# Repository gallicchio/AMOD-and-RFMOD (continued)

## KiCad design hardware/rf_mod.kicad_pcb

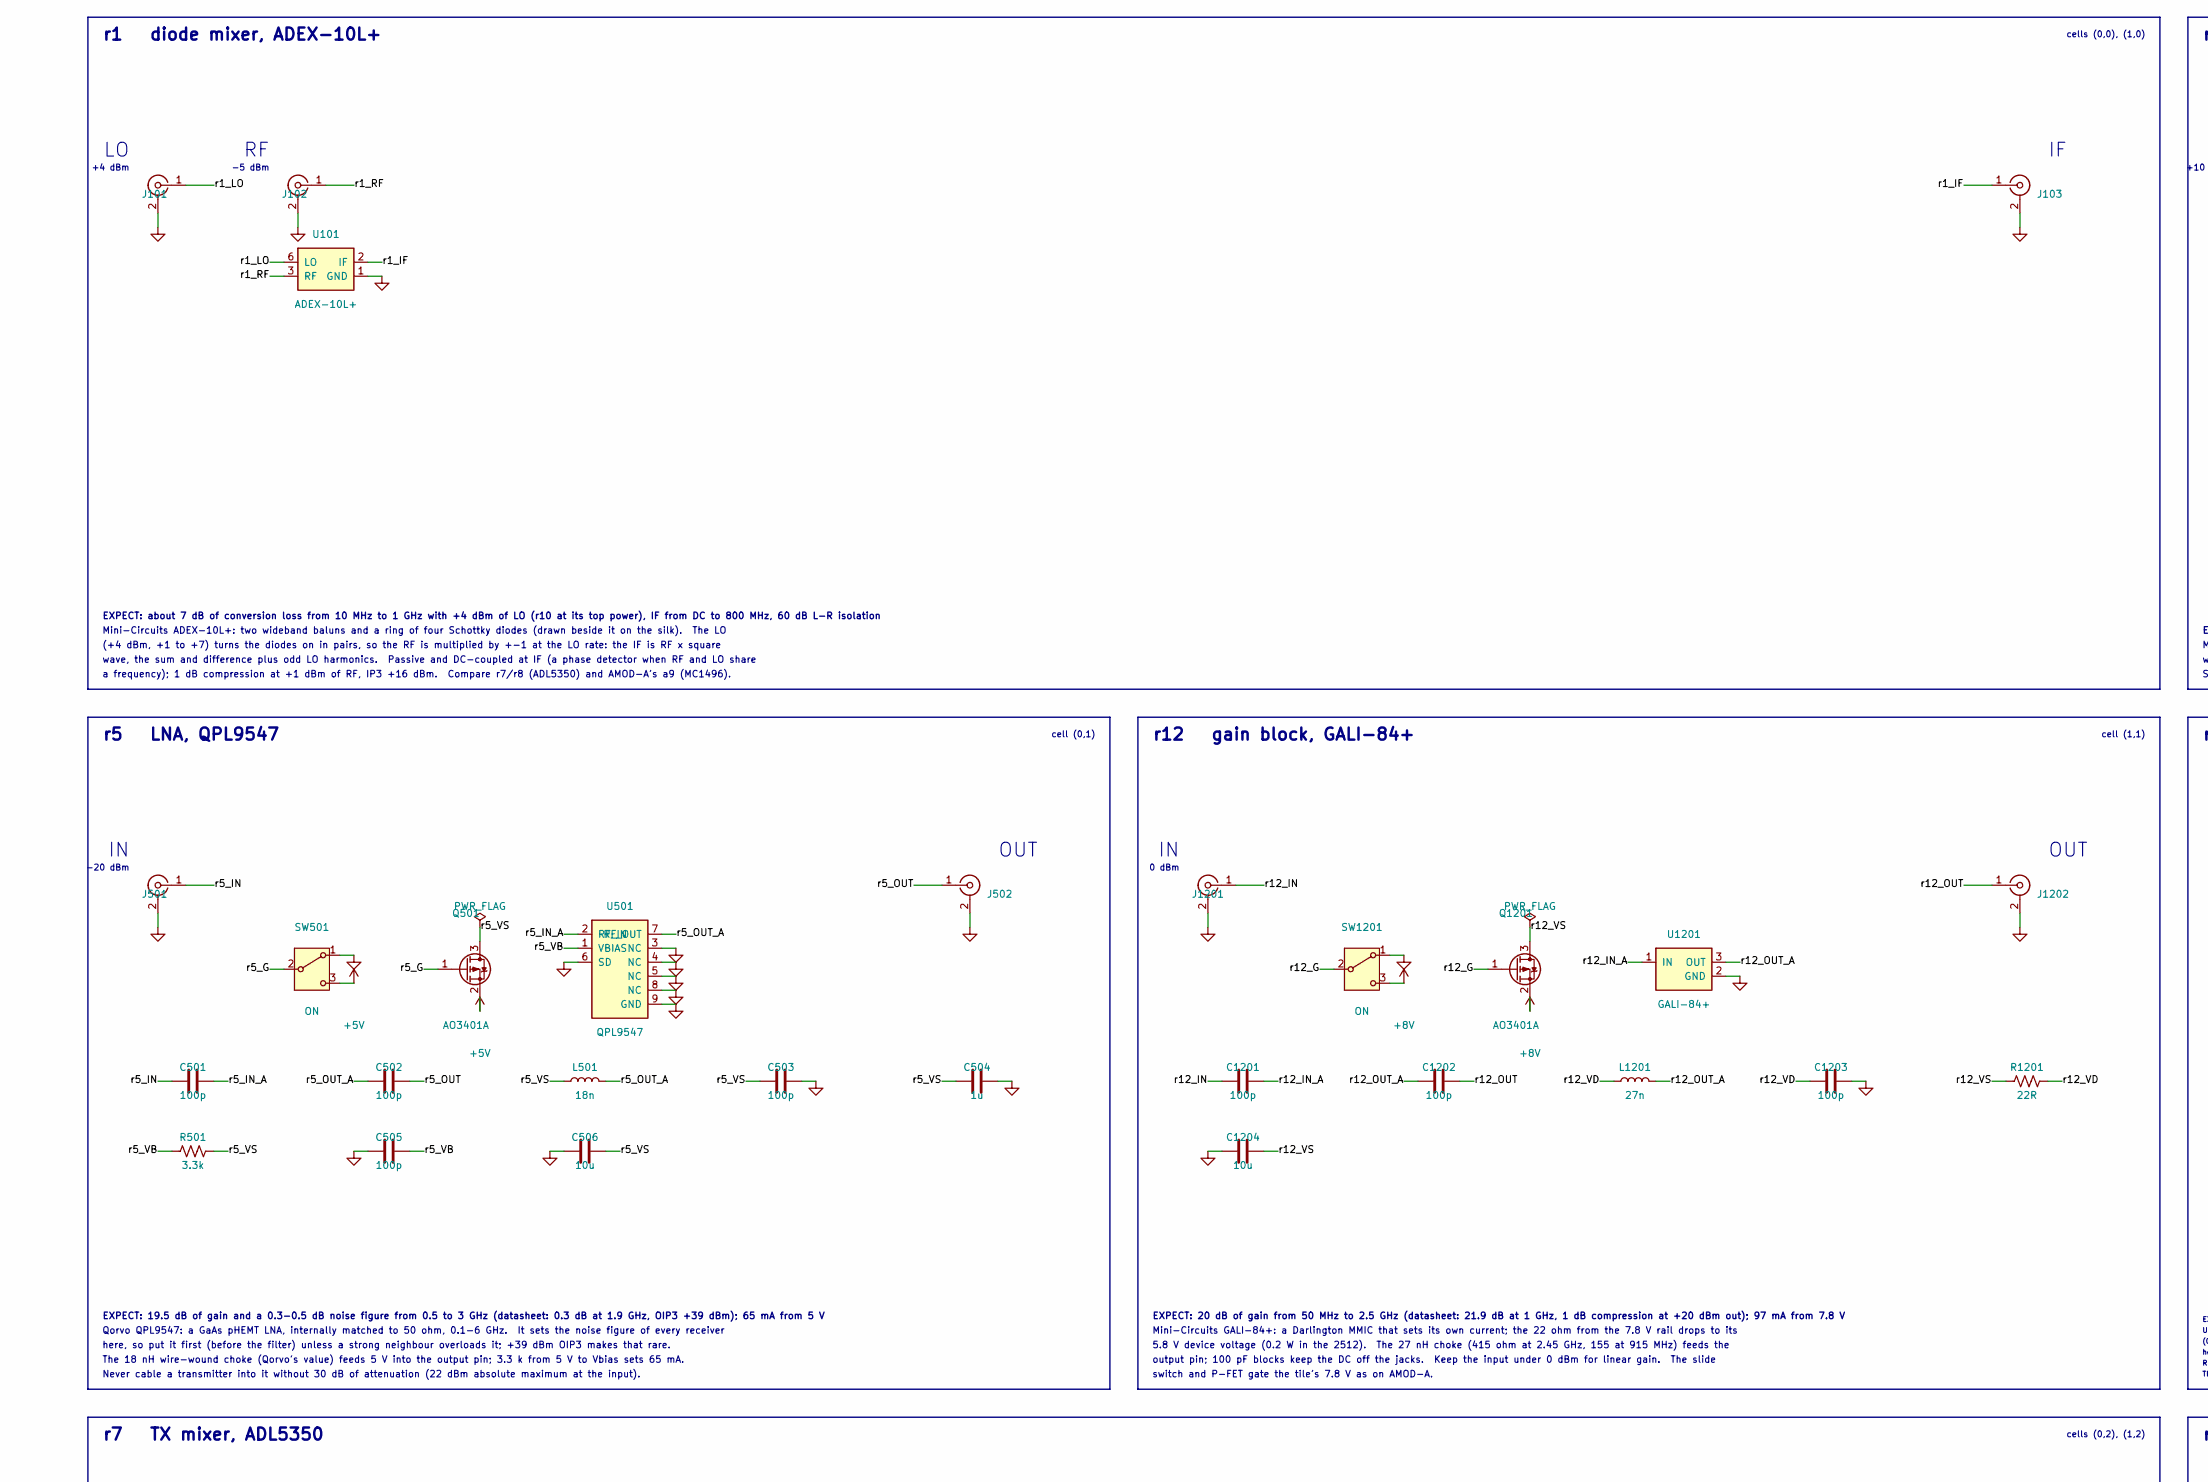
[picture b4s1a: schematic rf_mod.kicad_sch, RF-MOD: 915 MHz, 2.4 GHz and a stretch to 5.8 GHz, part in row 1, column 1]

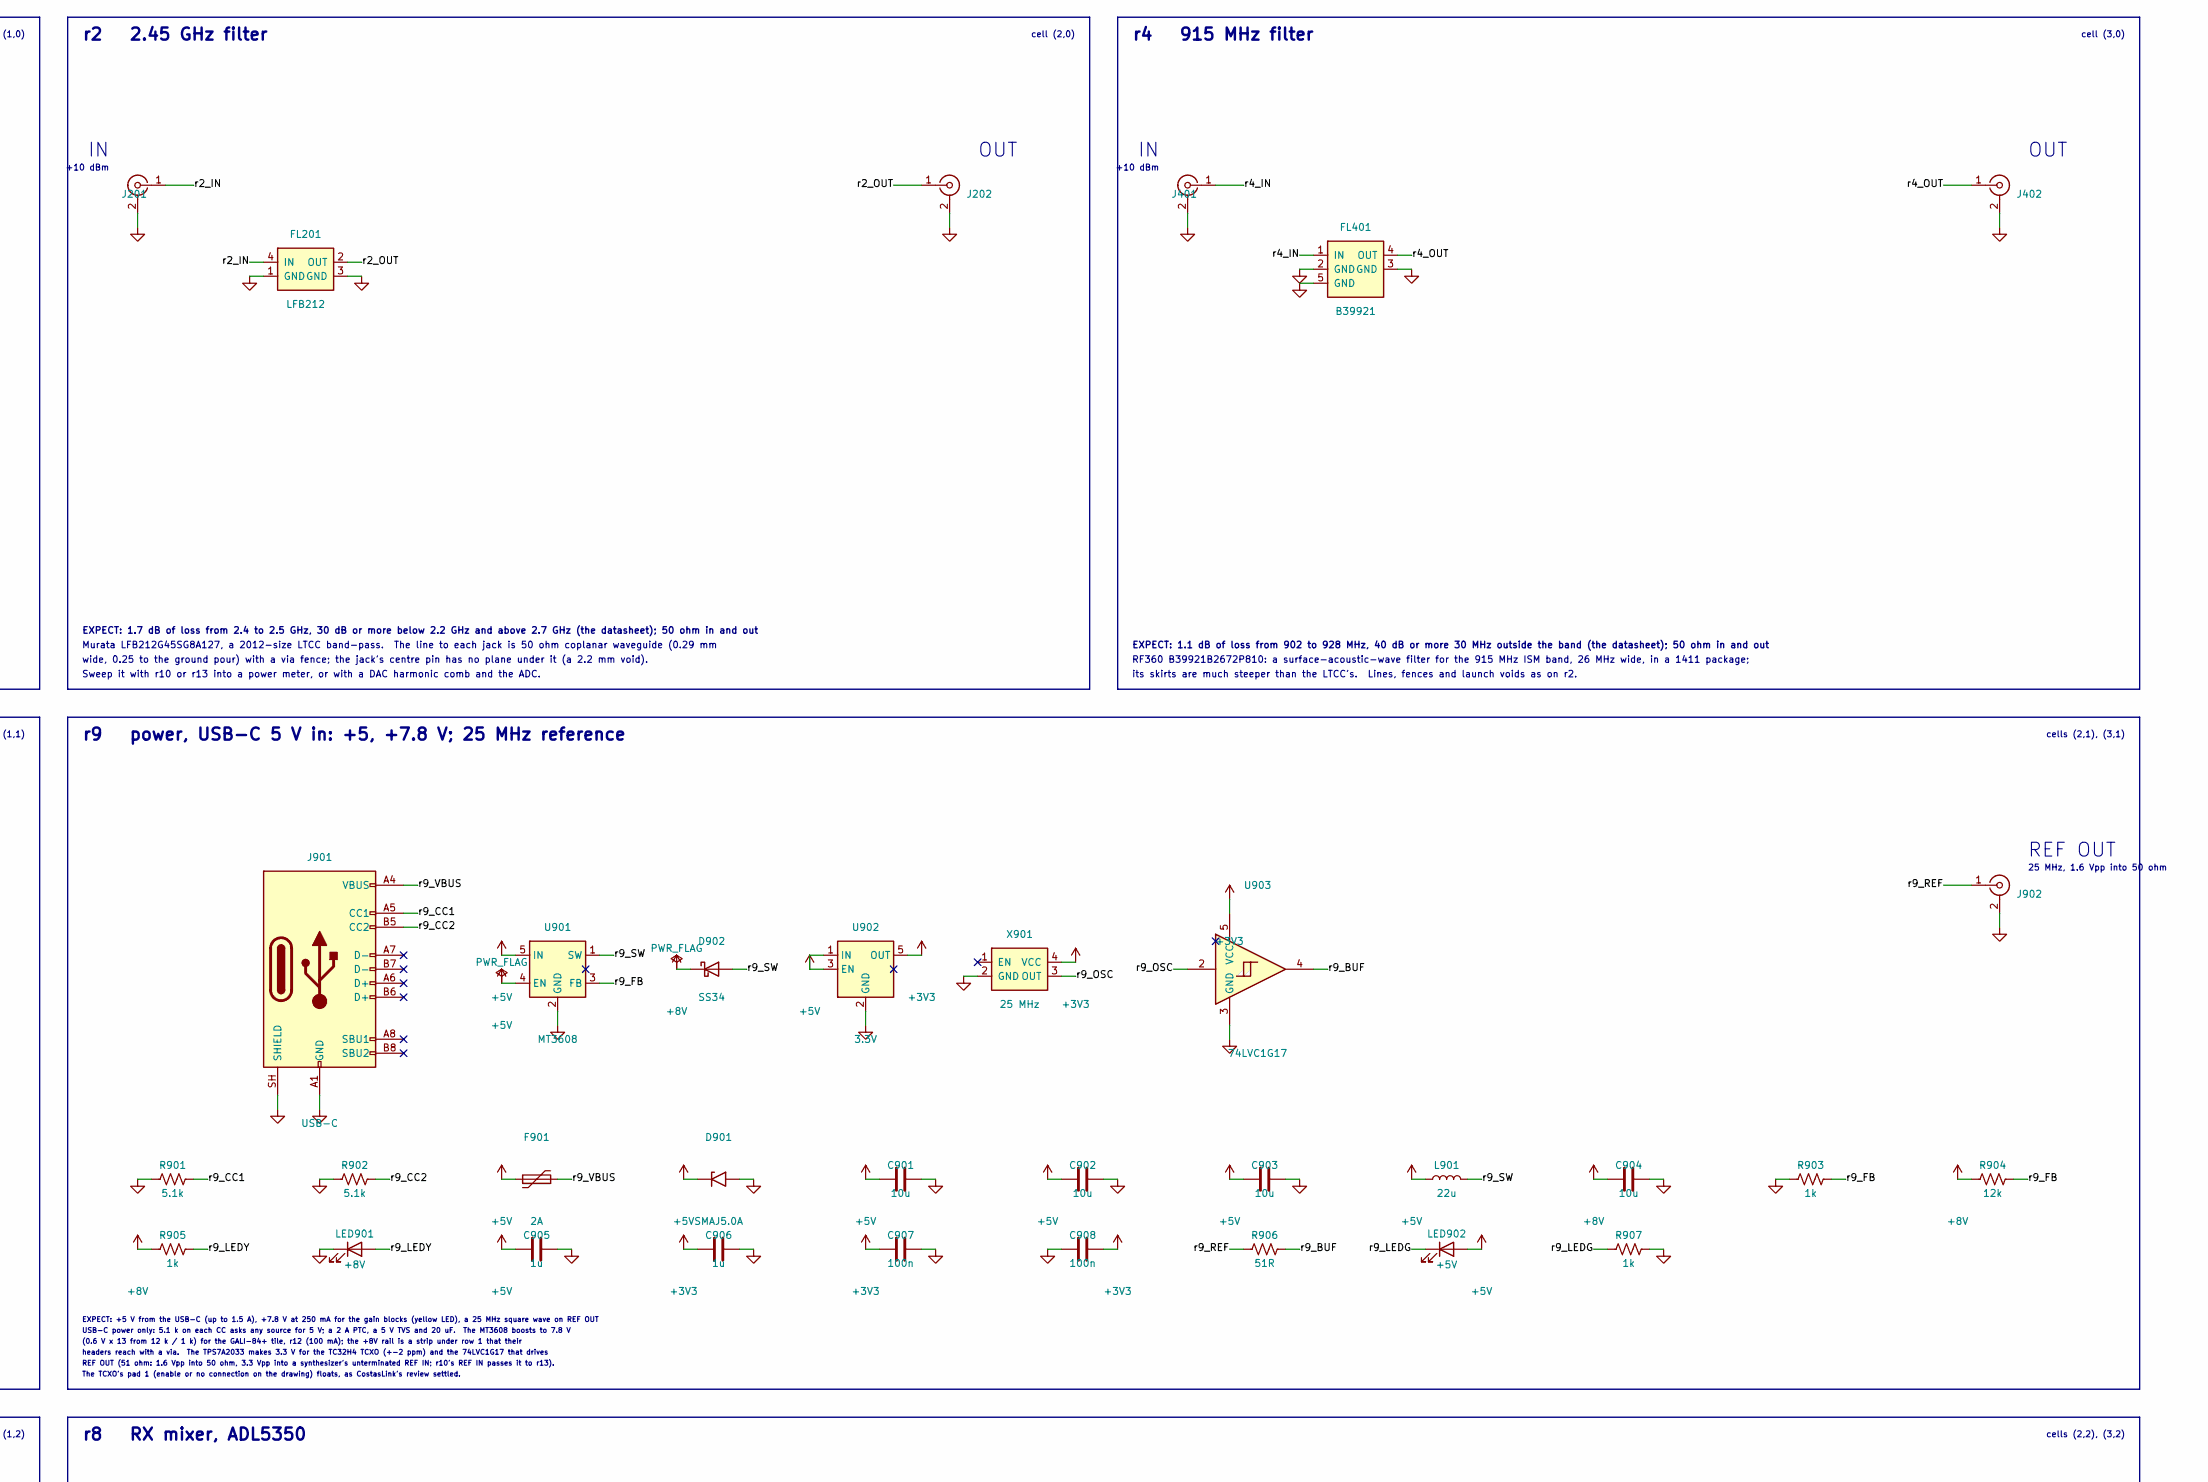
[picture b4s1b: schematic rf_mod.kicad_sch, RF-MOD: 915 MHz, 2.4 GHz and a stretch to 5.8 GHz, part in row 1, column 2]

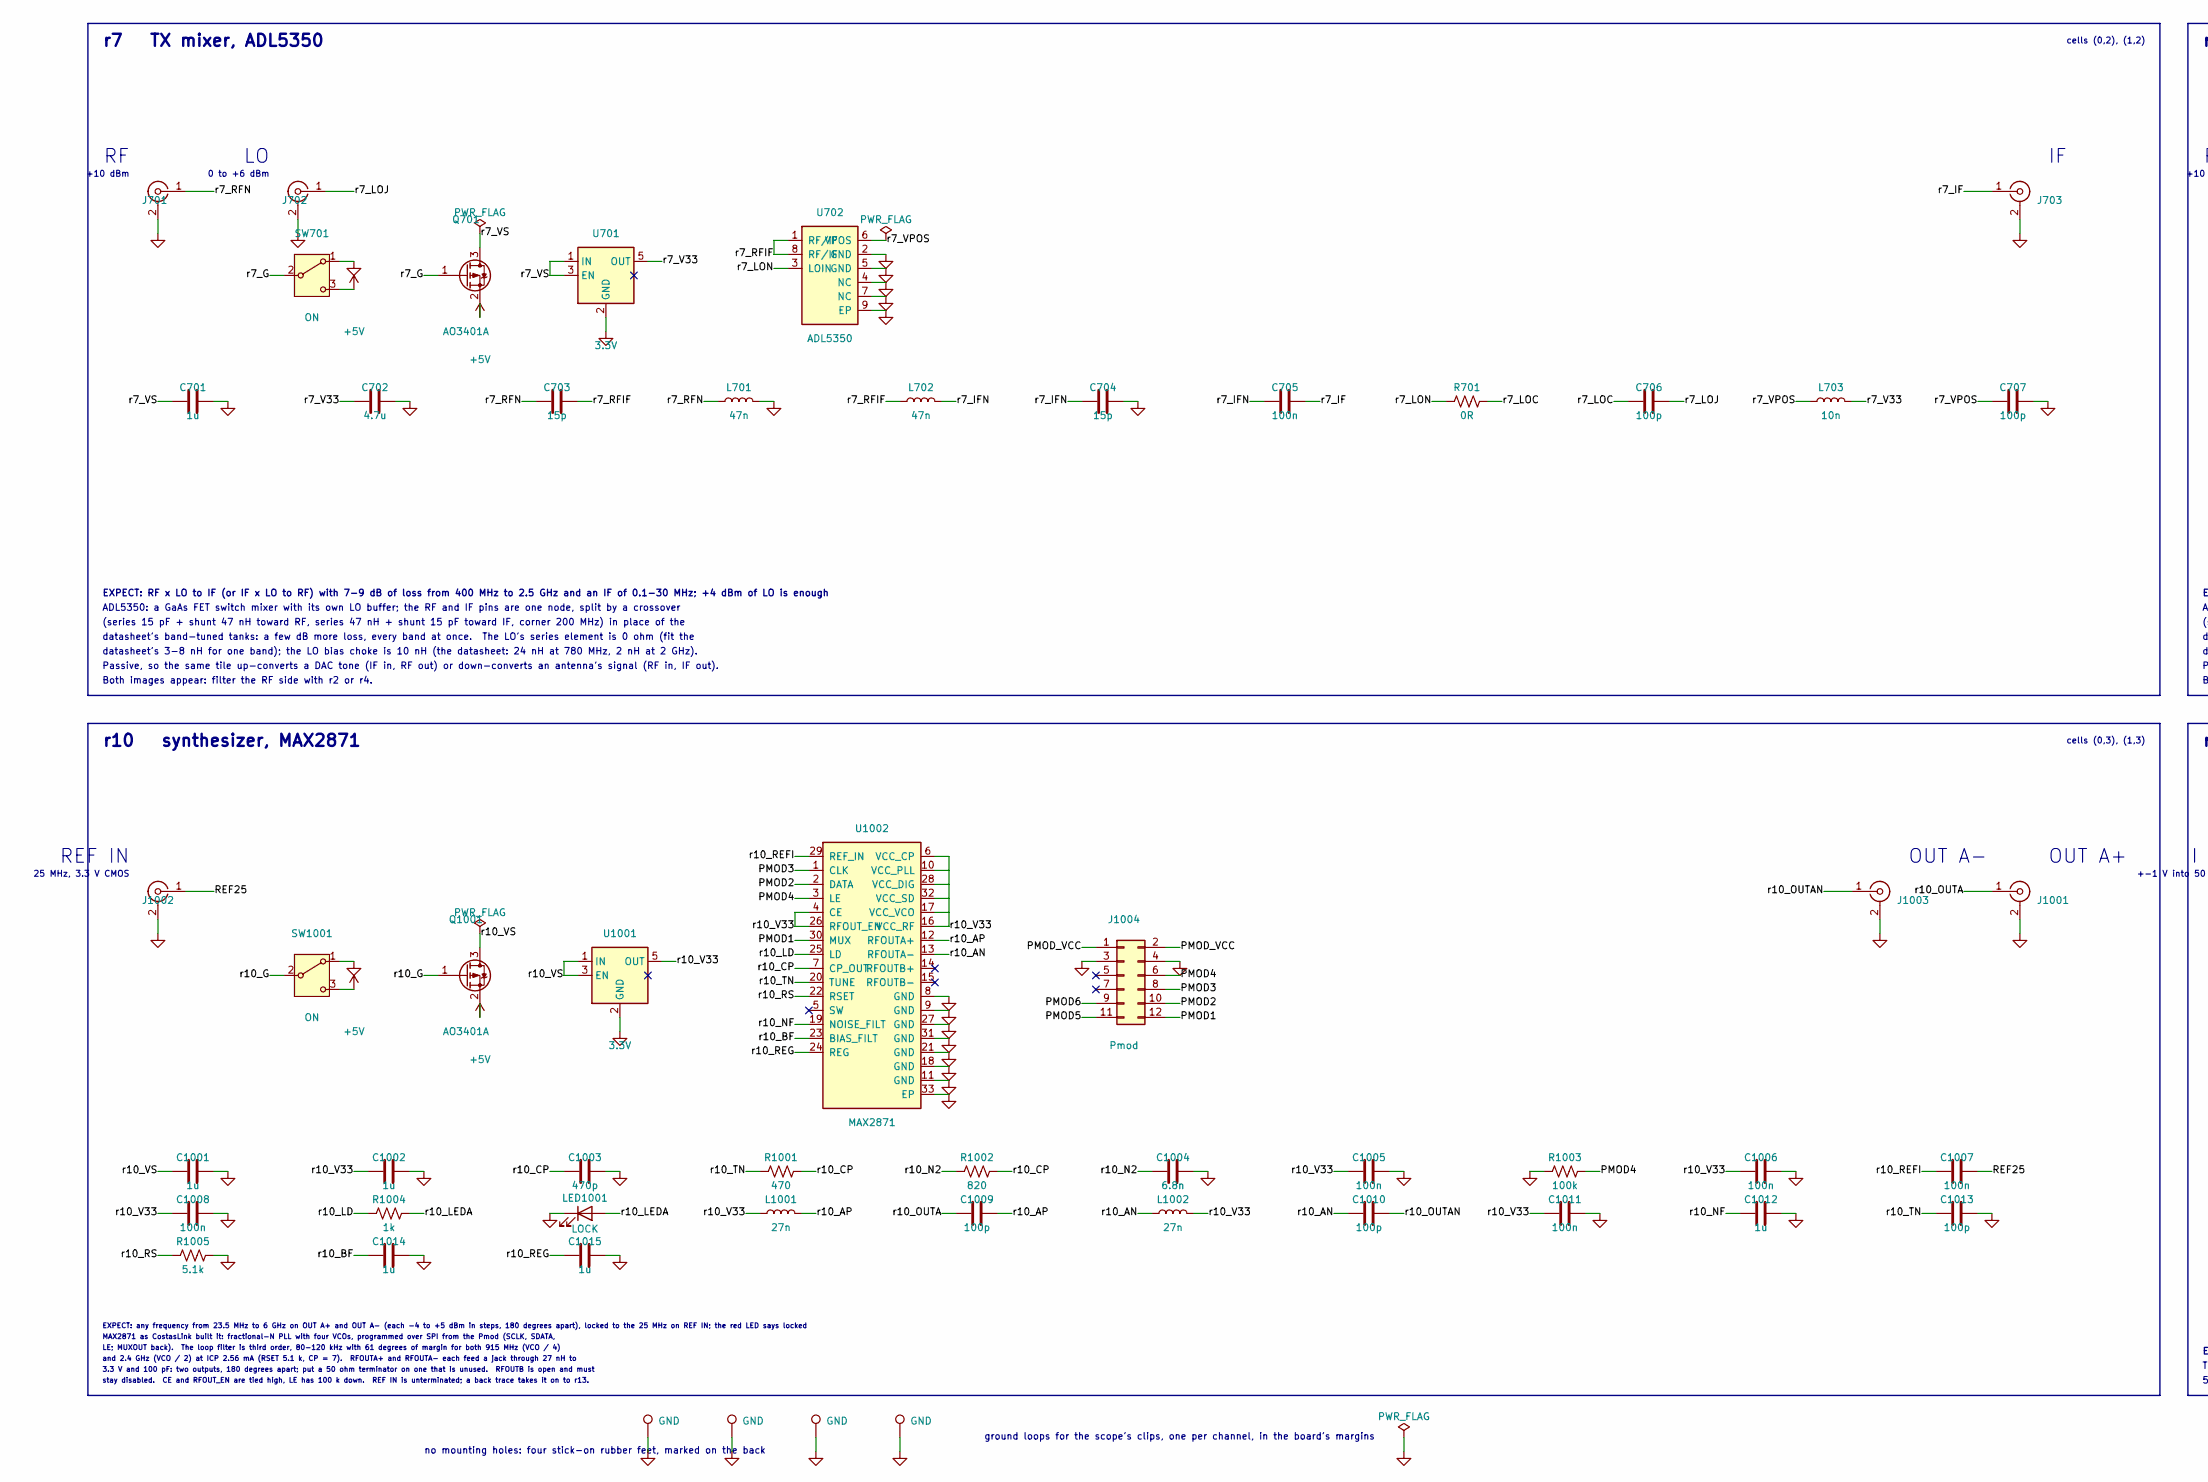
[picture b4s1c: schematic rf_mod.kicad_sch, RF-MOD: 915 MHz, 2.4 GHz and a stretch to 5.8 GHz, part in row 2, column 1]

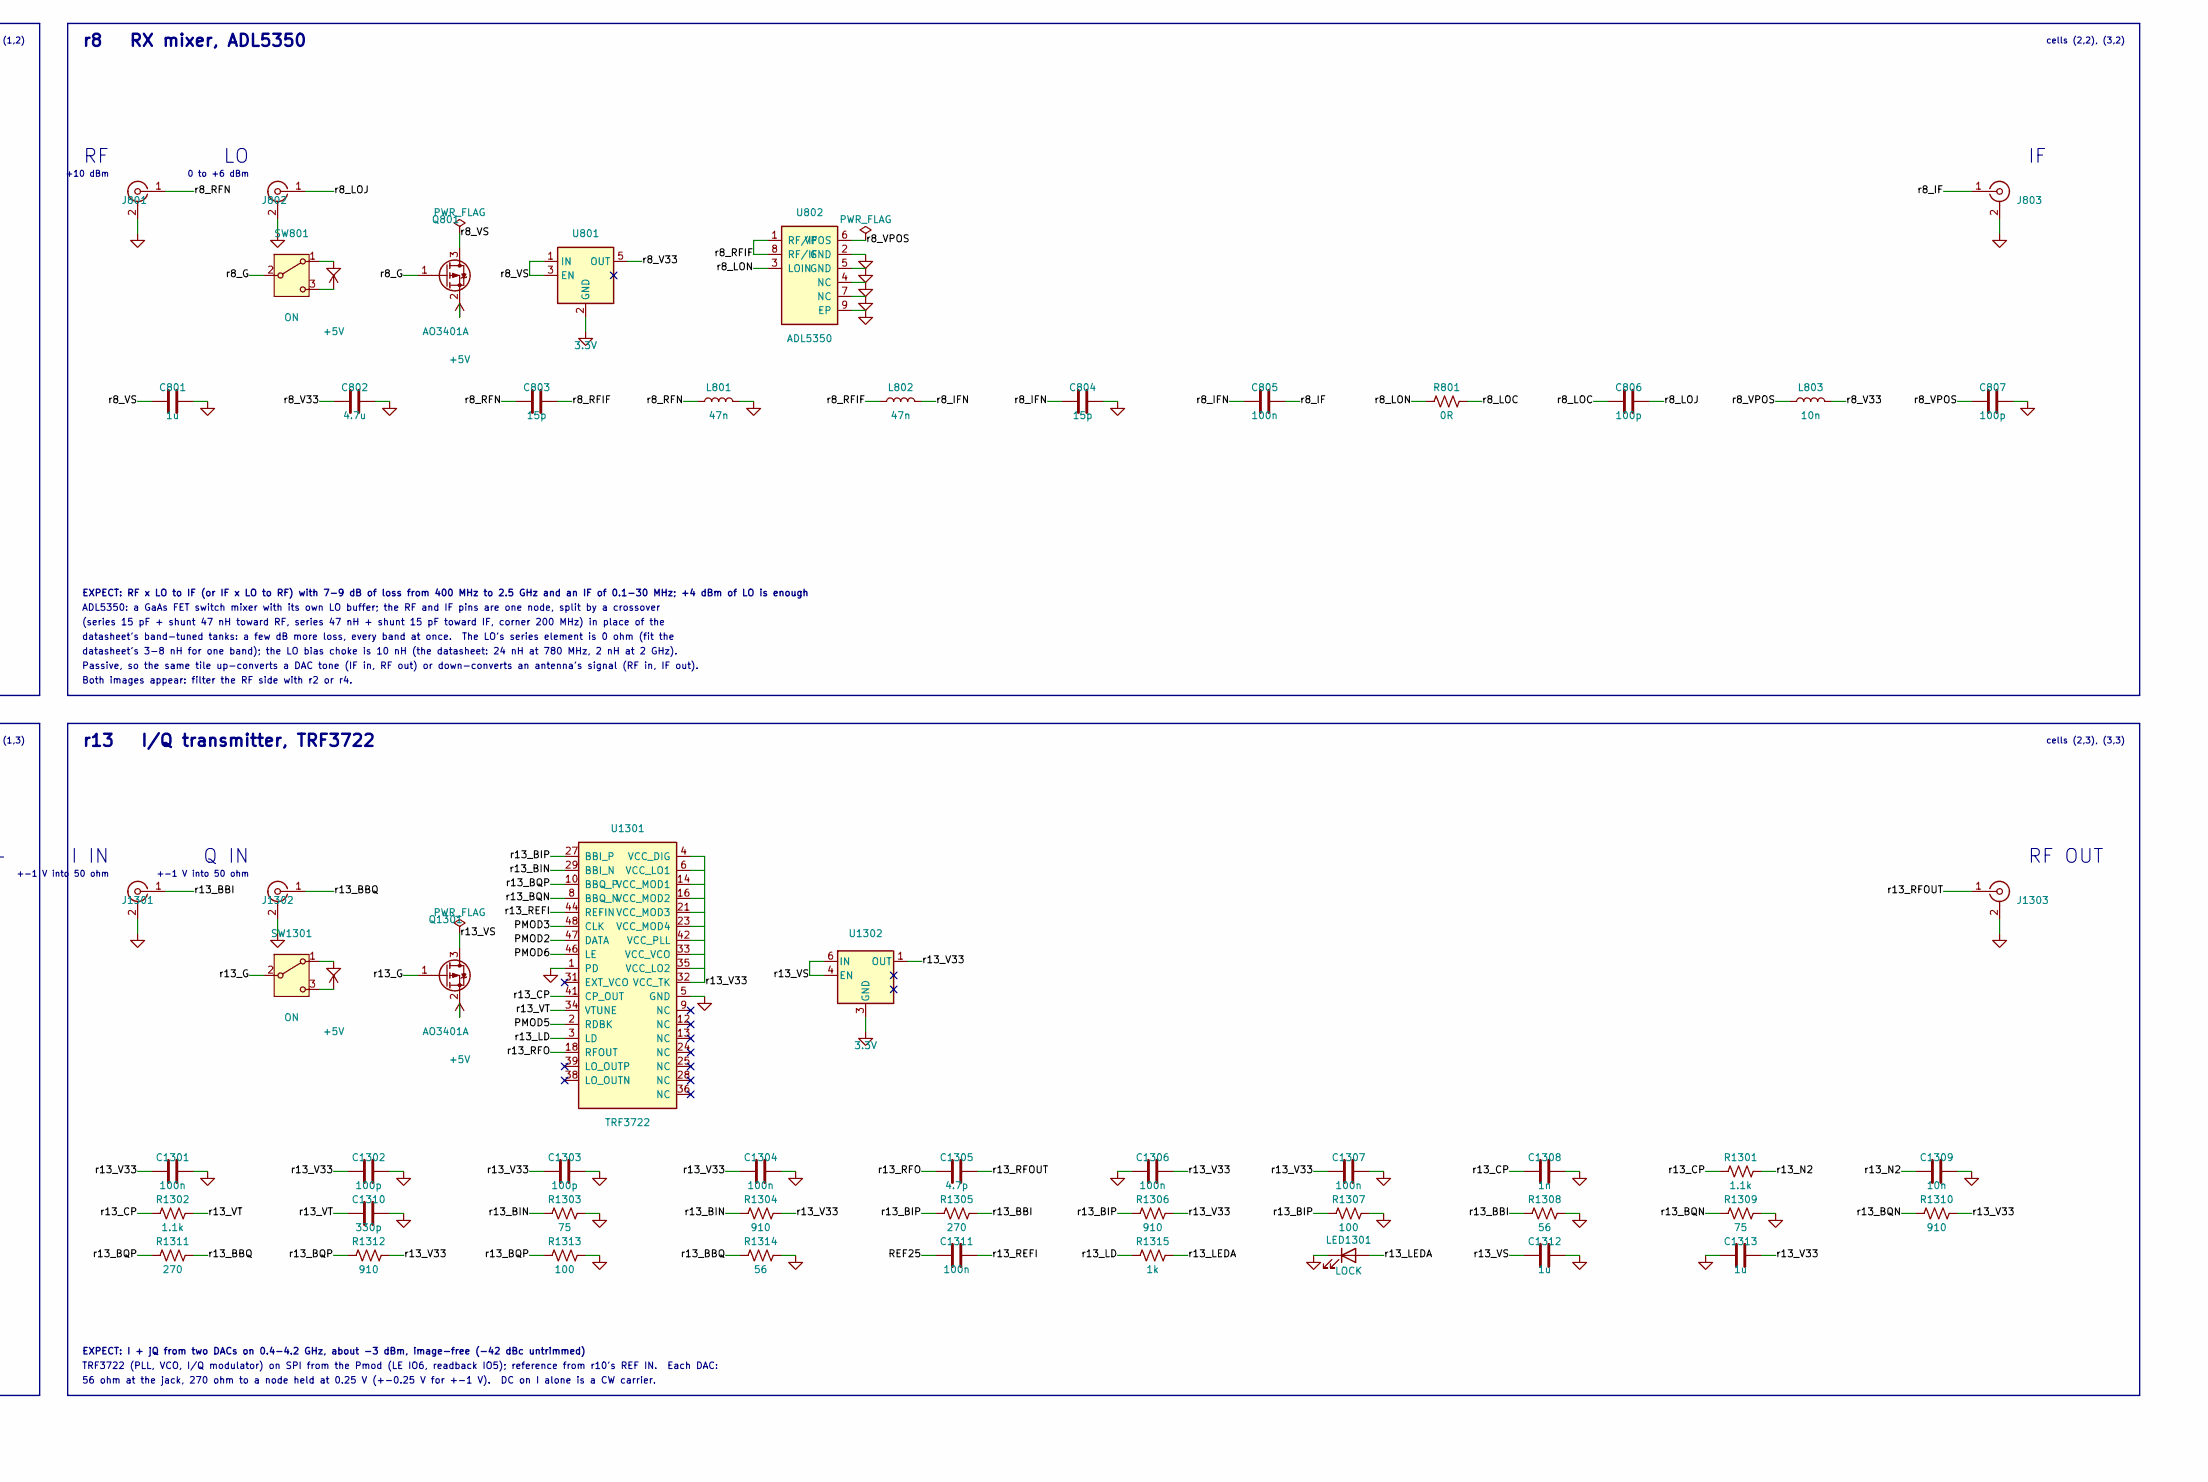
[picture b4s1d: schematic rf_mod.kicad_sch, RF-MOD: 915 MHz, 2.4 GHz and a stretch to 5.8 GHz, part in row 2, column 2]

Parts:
C501, C502, C503, C505, C706, C707, C806, C807, C1009, C1010, C1201, C1202, C1203, C1302, C1303: 100p; C_0402_1005Metric; MPN 0402CG101J500NT; LCSC C1546
C504, C1012, C1014, C1015: 1u; C_0402_1005Metric; MPN CL05A105KP5NNNC; LCSC C14445
C506, C901, C902, C903, C904, C1204: 10u; C_0805_2012Metric; MPN CL21A106KAYNNNE; LCSC C15850
C701, C801, C905, C906, C1001, C1002: 1u; C_0805_2012Metric; MPN CL21B105KBFNNNE; LCSC C28323
C702, C802: 4.7u; C_0805_2012Metric; MPN CL21A475KAQNNNE; LCSC C1779
C703, C704, C803, C804: 15p; C_0402_1005Metric; MPN 0402CG150J500NT; LCSC C1548
C705, C805, C1005, C1006, C1007, C1008, C1011, C1301, C1304, C1306, C1307, C1311: 100n; C_0402_1005Metric; MPN CL05B104KO5NNNC; LCSC C1525
C907, C908: 100n; C_0603_1608Metric; MPN CC0603KRX7R9BB104; LCSC C14663
C1003: 470p; C_0603_1608Metric; MPN 0603CG471J500NT; LCSC C36252
C1004: 6.8n; C_0603_1608Metric; MPN GRM1885C1H682JA01D; LCSC C162241
C1013: 100p; C_0603_1608Metric; MPN CL10C101JB8NNNC; LCSC C14858
C1305: 4.7p; C_0402_1005Metric; MPN 0402CG4R7C500NT; LCSC C1569
C1308: 1n; C_0402_1005Metric; MPN 0402B102K500NT; LCSC C1523
C1309: 10n; C_0402_1005Metric; MPN CL05B103KB5NNNC; LCSC C15195
C1310: 330p; C_0402_1005Metric; MPN 0402CG331J500NT; LCSC C190579
C1312, C1313: 1u; C_0603_1608Metric; MPN CL10A105KB8NNNC; LCSC C15849
D901: SMAJ5.0A; D_SMA; MPN SMAJ5.0A; LCSC C78401
D902: SS34; D_SMA; MPN SS34; LCSC C8678
F901: 2A; Fuse_1812_4532Metric; MPN MF-MSMF200-2; LCSC C210837
FL201: LFB212; Filter_LTCC_2012_LFB212; MPN LFB212G45SG8A127; LCSC C341536
FL401: B39921; Filter_SAW_1411-5P_B39921; MPN B39921B2672P810; LCSC C1518004
J101, J102, J103, J201, J202, J401, J402, J501, J502, J701, J702, J703, J801, J802, J803, J902, J1001, J1002, J1003, J1201, J1202, J1301, J1302, J1303: SMA; SMA_BWSMA-KE-Z001_Vertical; MPN BWSMA-KE-Z001; LCSC C496549
J901: USB-C; USB_C_Receptacle_HRO_TYPE-C-31-M-12; MPN TYPE-C-31-M-12; LCSC C165948
J1004: Pmod; PinHeader_2x06_P2.54mm_Horizontal_PZ254R-12-12P; MPN PZ254R-12-12P; LCSC C492434
L501: 18n; L_0402_1005Metric; MPN LQW15AN18NG00D; LCSC C91622
L701, L702, L801, L802: 47n; L_0402_1005Metric; MPN LQW15AN47NJ00D; LCSC C192855
L703, L803: 10n; L_0402_1005Metric; MPN LQW15AN10NJ00D; LCSC C184029
L901: 22u; L_4x4_XRNR4030; MPN XRNR4030-22uH/M; LCSC C5289362
L1001, L1002, L1201: 27n; L_0402_1005Metric; MPN LQW15AN27NG80D; LCSC C882469
LED901: +8V; LED_0805_2012Metric_Kbar; MPN KT-0805Y; LCSC C2296
LED902: +5V; LED_0805_2012Metric_Kbar; MPN KT-0805G; LCSC C2297
LED1001, LED1301: LOCK; LED_0805_2012Metric_Kbar; MPN NCD0805R1; LCSC C84256
Q501, Q701, Q801, Q1001, Q1201, Q1301: AO3401A; SOT-23; MPN AO3401A; LCSC C15127
R501: 3.3k; R_0402_1005Metric; MPN 0402WGF3301TCE; LCSC C25890
R701, R801: 0R; R_0402_1005Metric; MPN 0402WGF0000TCE; LCSC C17168
R901, R902: 5.1k; R_0805_2012Metric; MPN 0805W8F5101T5E; LCSC C27834
R903, R1004, R1315: 1k; R_0402_1005Metric; MPN 0402WGF1001TCE; LCSC C11702
R904: 12k; R_0402_1005Metric; MPN 0402WGF1202TCE; LCSC C25752
R905, R907: 1k; R_0805_2012Metric; MPN 0805W8F1001T5E; LCSC C17513
R906: 51R; R_0402_1005Metric; MPN 0402WGF510JTCE; LCSC C25125
R1001: 470; R_0402_1005Metric; MPN 0402WGF4700TCE; LCSC C25117
R1002: 820; R_0402_1005Metric; MPN 0402WGF8200TCE; LCSC C25135
R1003: 100k; R_0402_1005Metric; MPN 0402WGF1003TCE; LCSC C25741
R1005: 5.1k; R_0402_1005Metric; MPN 0402WGF5101TCE; LCSC C25905
R1201: 22R; R_2512_6332Metric; MPN 25121WJ0220T4E; LCSC C27258
R1301, R1302: 1.1k; R_0402_1005Metric; MPN 0402WGF1101TCE; LCSC C25860
R1303, R1309: 75; R_0402_1005Metric; MPN 0402WGF750JTCE; LCSC C25133
R1304, R1306, R1310, R1312: 910; R_0402_1005Metric; MPN 0402WGF9100TCE; LCSC C44933
R1305, R1311: 270; R_0402_1005Metric; MPN 0402WGF2700TCE; LCSC C25099
R1307, R1313: 100; R_0402_1005Metric; MPN 0402WGF1000TCE; LCSC C25076
R1308, R1314: 56; R_0402_1005Metric; MPN 0402WGF560JTCE; LCSC C25127
SW501, SW701, SW801, SW1001, SW1201, SW1301: ON; SW_SPDT_Shouhan_MSK12C02; MPN MSK12C02; LCSC C431540
TP9901, TP9902, TP9903, TP9904: GND; TestPoint_Loop_RH-5019; MPN RH-5019; LCSC C5199800
U101: ADEX-10L+; MiniCircuits_CD542_ADEX-10L; MPN ADEX-10L+; LCSC C118997
U501: QPL9547; DFN-8-1EP_2x2mm_P0.5mm_EP0.9x1.6mm; MPN QPL9547TR7; LCSC C5367093
U701, U801, U902, U1001: 3.3V; SOT-23-5; MPN TPS7A2033PDBVR; LCSC C2862740
U702, U802: ADL5350; LFCSP-8_2x3mm_P0.5mm_ADL5350; MPN ADL5350ACPZ-R7; LCSC C206667
U901: MT3608; SOT-23-6; MPN MT3608; LCSC C84817
U903: 74LVC1G17; SOT-23-5; MPN SN74LVC1G17DBVR; LCSC C7836
U1002: MAX2871; QFN-32-1EP_5x5mm_P0.5mm_EP3.1x3.1mm; MPN MAX2871ETJ+T; LCSC C7458627
U1201: GALI-84+; SOT-89-3; MPN GALI-84+; LCSC C3193261
U1301: TRF3722; Texas_RGZ0048A_VQFN-48-1EP_7x7mm_P0.5mm_EP5.15x5.15mm; MPN TRF3722IRGZR; LCSC C1850395
U1302: 3.3V; WSON-6-1EP_2x2mm_P0.65mm_EP1x1.6mm; MPN TLV75733PDRVR; LCSC C2868428
X901: 25 MHz; Crystal_SMD_3225-4Pin_3.2x2.5mm; MPN TC32H4-25.000-33GNDTNL; LCSC C5119013

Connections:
+3V3: C906.1, C907.1, C908.2, U902.5 (OUT), U903.5 (VCC), X901.4 (VCC)
+5V: C901.1, C902.1, C903.1, C905.1, D901.1 (A1), F901.1, L901.1, LED902.2 (A), Q501.2 (S), Q701.2 (S), Q801.2 (S), Q1001.2 (S), Q1301.2 (S), SW501.3 (C), SW701.3 (C), SW801.3 (C), SW1001.3 (C), SW1301.3 (C), U901.4 (EN), U901.5 (IN), U902.1 (IN), U902.3 (EN)
+8V: C904.1, D902.1 (K), Q1201.2 (S), R904.1, R905.1, SW1201.3 (C)
/PMOD1: J1004.12, U1002.30 (MUX)
/PMOD2: J1004.10, U1002.2 (DATA), U1301.47 (DATA)
/PMOD3: J1004.8, U1002.1 (CLK), U1301.48 (CLK)
/PMOD4: J1004.6, R1003.2, U1002.3 (LE)
/PMOD5: J1004.11, U1301.2 (RDBK)
/PMOD6: J1004.9, U1301.46 (LE)
/PMOD_VCC: J1004.1, J1004.2
/REF25: C1007.2, C1311.1, J1002.1 (In)
/r1_IF: J103.1 (In), U101.2 (IF)
/r1_LO: J101.1 (In), U101.6 (LO)
/r1_RF: J102.1 (In), U101.3 (RF)
/r2_IN: FL201.4 (IN), J201.1 (In)
/r2_OUT: FL201.2 (OUT), J202.1 (In)
/r4_IN: FL401.1 (IN), J401.1 (In)
/r4_OUT: FL401.4 (OUT), J402.1 (In)
/r5_G: Q501.1 (G), SW501.2 (B)
/r5_IN: C501.1, J501.1 (In)
/r5_IN_A: C501.2, U501.2 (RF_IN)
/r5_OUT: C502.2, J502.1 (In)
/r5_OUT_A: C502.1, L501.2, U501.7 (RF_OUT)
/r5_VB: C505.2, R501.1, U501.1 (VBIAS)
/r5_VS: C503.1, C504.1, C506.2, L501.1, Q501.3 (D), R501.2
/r7_G: Q701.1 (G), SW701.2 (B)
/r7_IF: C705.2, J703.1 (In)
/r7_IFN: C704.1, C705.1, L702.2
/r7_LOC: C706.1, R701.2
/r7_LOJ: C706.2, J702.1 (In)
/r7_LON: R701.1, U702.3 (LOIN)
/r7_RFIF: C703.2, L702.1, U702.1 (RF/IF), U702.8 (RF/IF)
/r7_RFN: C703.1, J701.1 (In), L701.1
/r7_V33: C702.1, L703.2, U701.5 (OUT)
/r7_VPOS: C707.1, L703.1, U702.6 (VPOS)
/r7_VS: C701.1, Q701.3 (D), U701.1 (IN), U701.3 (EN)
/r8_G: Q801.1 (G), SW801.2 (B)
/r8_IF: C805.2, J803.1 (In)
/r8_IFN: C804.1, C805.1, L802.2
/r8_LOC: C806.1, R801.2
/r8_LOJ: C806.2, J802.1 (In)
/r8_LON: R801.1, U802.3 (LOIN)
/r8_RFIF: C803.2, L802.1, U802.1 (RF/IF), U802.8 (RF/IF)
/r8_RFN: C803.1, J801.1 (In), L801.1
/r8_V33: C802.1, L803.2, U801.5 (OUT)
/r8_VPOS: C807.1, L803.1, U802.6 (VPOS)
/r8_VS: C801.1, Q801.3 (D), U801.1 (IN), U801.3 (EN)
/r9_BUF: R906.2, U903.4
/r9_CC1: J901.A5 (CC1), R901.2
/r9_CC2: J901.B5 (CC2), R902.2
/r9_FB: R903.2, R904.2, U901.3 (FB)
/r9_LEDG: LED902.1 (K), R907.1
/r9_LEDY: LED901.2 (A), R905.2
/r9_OSC: U903.2, X901.3 (OUT)
/r9_REF: J902.1 (In), R906.1
/r9_SW: D902.2 (A), L901.2, U901.1 (SW)
/r9_VBUS: F901.2, J901.A4 (VBUS), J901.A9 (VBUS), J901.B4 (VBUS), J901.B9 (VBUS)
/r10_AN: C1010.1, L1002.1, U1002.13 (RFOUTA-)
/r10_AP: C1009.2, L1001.2, U1002.12 (RFOUTA+)
/r10_BF: C1014.1, U1002.23 (BIAS_FILT)
/r10_CP: C1003.1, R1001.2, R1002.2, U1002.7 (CP_OUT)
/r10_G: Q1001.1 (G), SW1001.2 (B)
/r10_LD: R1004.1, U1002.25 (LD)
/r10_LEDA: LED1001.2 (A), R1004.2
/r10_N2: C1004.1, R1002.1
/r10_NF: C1012.1, U1002.19 (NOISE_FILT)
/r10_OUTA: C1009.1, J1001.1 (In)
/r10_OUTAN: C1010.2, J1003.1 (In)
/r10_REFI: C1007.1, U1002.29 (REF_IN)
/r10_REG: C1015.1, U1002.24 (REG)
/r10_RS: R1005.1, U1002.22 (RSET)
/r10_TN: C1013.1, R1001.1, U1002.20 (TUNE)
/r10_V33: C1002.1, C1005.1, C1006.1, C1008.1, C1011.1, L1001.1, L1002.2, U1001.5 (OUT), U1002.4 (CE), U1002.6 (VCC_CP), U1002.10 (VCC_PLL), U1002.16 (VCC_RF), U1002.17 (VCC_VCO), U1002.26 (RFOUT_EN), U1002.28 (VCC_DIG), U1002.32 (VCC_SD)
/r10_VS: C1001.1, Q1001.3 (D), U1001.1 (IN), U1001.3 (EN)
/r12_G: Q1201.1 (G), SW1201.2 (B)
/r12_IN: C1201.1, J1201.1 (In)
/r12_IN_A: C1201.2, U1201.1 (IN)
/r12_OUT: C1202.2, J1202.1 (In)
/r12_OUT_A: C1202.1, L1201.2, U1201.3 (OUT)
/r12_VD: C1203.1, L1201.1, R1201.2
/r12_VS: C1204.2, Q1201.3 (D), R1201.1
/r13_BBI: J1301.1 (In), R1305.2, R1308.1
/r13_BBQ: J1302.1 (In), R1311.2, R1314.1
/r13_BIN: R1303.1, R1304.1, U1301.29 (BBI_N)
/r13_BIP: R1305.1, R1306.1, R1307.1, U1301.27 (BBI_P)
/r13_BQN: R1309.1, R1310.1, U1301.8 (BBQ_N)
/r13_BQP: R1311.1, R1312.1, R1313.1, U1301.10 (BBQ_P)
/r13_CP: C1308.1, R1301.1, R1302.1, U1301.41 (CP_OUT)
/r13_G: Q1301.1 (G), SW1301.2 (B)
/r13_LD: R1315.1, U1301.3 (LD)
/r13_LEDA: LED1301.2 (A), R1315.2
/r13_N2: C1309.1, R1301.2
/r13_REFI: C1311.2, U1301.44 (REFIN)
/r13_RFO: C1305.1, U1301.18 (RFOUT)
/r13_RFOUT: C1305.2, J1303.1 (In)
/r13_V33: C1301.1, C1302.1, C1303.1, C1304.1, C1306.2, C1307.1, C1313.2, R1304.2, R1306.2, R1310.2, R1312.2, U1301.4 (VCC_DIG), U1301.6 (VCC_LO1), U1301.14 (VCC_MOD1), U1301.16 (VCC_MOD2), U1301.21 (VCC_MOD3), U1301.23 (VCC_MOD4), U1301.32 (VCC_TK), U1301.33 (VCC_VCO), U1301.35 (VCC_LO2), U1301.42 (VCC_PLL), U1302.1 (OUT)
/r13_VS: C1312.1, Q1301.3 (D), U1302.4 (EN), U1302.6 (IN)
/r13_VT: C1310.1, R1302.2, U1301.34 (VTUNE)
GND: C503.2, C504.2, C505.1, C506.1, C701.2, C702.2, C704.2, C707.2, C801.2, C802.2, C804.2, C807.2, C901.2, C902.2, C903.2, C904.2, C905.2, C906.2, C907.2, C908.1, C1001.2, C1002.2, C1003.2, C1004.2, C1005.2, C1006.2, C1008.2, C1011.2, C1012.2, C1013.2, C1014.2, C1015.2, C1203.2, C1204.1, C1301.2, C1302.2, C1303.2, C1304.2, C1306.1, C1307.2, C1308.2, C1309.2, C1310.2, C1312.2, C1313.1, D901.2 (A2), FL201.1 (GND), FL201.3 (GND), FL401.2 (GND), FL401.3 (GND), FL401.5 (GND), J101.2 (Ext), J102.2 (Ext), J103.2 (Ext), J201.2 (Ext), J202.2 (Ext), J401.2 (Ext), J402.2 (Ext), J501.2 (Ext), J502.2 (Ext), J701.2 (Ext), J702.2 (Ext), J703.2 (Ext), J801.2 (Ext), J802.2 (Ext), J803.2 (Ext), J901.A1 (GND), J901.A12 (GND), J901.B1 (GND), J901.B12 (GND), J901.SH (SHIELD), J902.2 (Ext), J1001.2 (Ext), J1002.2 (Ext), J1003.2 (Ext), J1004.3, J1004.4, J1201.2 (Ext), J1202.2 (Ext), J1301.2 (Ext), J1302.2 (Ext), J1303.2 (Ext), L701.2, L801.2, LED901.1 (K), LED1001.1 (K), LED1301.1 (K), R901.1, R902.1, R903.1, R907.2, R1003.1, R1005.2, R1303.2, R1307.2, R1308.2, R1309.2, R1313.2, R1314.2, SW501.1 (A), SW701.1 (A), SW801.1 (A), SW1001.1 (A), SW1201.1 (A), SW1301.1 (A), TP9901.1, TP9902.1, TP9903.1, TP9904.1, U101.1 (GND), U101.4 (GND), U101.5 (GND), U501.3 (NC), U501.4 (NC), U501.5 (NC), U501.6 (SD), U501.8 (NC), U501.9 (GND), U701.2 (GND), U702.2 (GND), U702.4 (NC), U702.5 (GND), U702.7 (NC), U702.9 (EP), U801.2 (GND), U802.2 (GND), U802.4 (NC), U802.5 (GND), U802.7 (NC), U802.9 (EP), U901.2 (GND), U902.2 (GND), U903.3 (GND), U1001.2 (GND), U1002.8 (GND), U1002.9 (GND), U1002.11 (GND), U1002.18 (GND), U1002.21 (GND), U1002.27 (GND), U1002.31 (GND), U1002.33 (EP), U1201.2 (GND), U1301.1 (PD), U1301.5 (GND), U1301.7 (GND), U1301.11 (GND), U1301.15 (GND), U1301.17 (GND), U1301.19 (GND), U1301.20 (GND), U1301.22 (GND), U1301.26 (GND), U1301.30 (GND), U1301.37 (GND), U1301.40 (GND), U1301.43 (GND), U1301.45 (GND), U1301.49 (GND), U1302.3 (GND), U1302.7 (GND), X901.2 (GND)

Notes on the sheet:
+-1 V into 50 ohm
here, so put it first (before the filter) unless a strong neighbour overloads it; +39 dBm OIP3 makes that rare.
cells (2,1), (3,1)
+10 dBm
56 ohm at the jack, 270 ohm to a node held at 0.25 V (+-0.25 V for +-1 V). DC on I alone is a CW carrier.
OUT
cells (2,2), (3,2)
ADL5350: a GaAs FET switch mixer with its own LO buffer; the RF and IF pins are one node, split by a crossover
EXPECT: I + jQ from two DACs on 0.4-4.2 GHz, about -3 dBm, image-free (-42 dBc untrimmed)
REF OUT
OUT A-
datasheet's band-tuned tanks: a few dB more loss, every band at once. The LO's series element is 0 ohm (fit the
r2 2.45 GHz filter
cell (2,0)
switch and P-FET gate the tile's 7.8 V as on AMOD-A.
(0.6 V x 13 from 12 k / 1 k) for the GALI-84+ tile, r12 (100 mA); the +8V rail is a strip under row 1 that their
r7 TX mixer, ADL5350
I IN
Q IN
cell (0,1)
Qorvo QPL9547: a GaAs pHEMT LNA, internally matched to 50 ohm, 0.1-6 GHz. It sets the noise figure of every receiver
Both images appear: filter the RF side with r2 or r4.
r1 diode mixer, ADEX-10L+
cells (0,0), (1,0)
25 MHz, 3.3 V CMOS
r13 I/Q transmitter, TRF3722
r12 gain block, GALI-84+
EXPECT: any frequency from 23.5 MHz to 6 GHz on OUT A+ and OUT A- (each -4 to +5 dBm in steps, 180 degrees apart), locked to the 25 MHz on REF IN; the red LED says locked
REF IN
cells (2,3), (3,3)
stay disabled. CE and RFOUT_EN are tied high, LE has 100 k down. REF IN is unterminated; a back trace takes it on to r13.
-20 dBm
Sweep it with r10 or r13 into a power meter, or with a DAC harmonic comb and the ADC.
0 to +6 dBm
5.8 V device voltage (0.2 W in the 2512). The 27 nH choke (415 ohm at 2.45 GHz, 155 at 915 MHz) feeds the
wave, the sum and difference plus odd LO harmonics. Passive and DC-coupled at IF (a phase detector when RF and LO share
cells (0,3), (1,3)
ground loops for the scope's clips, one per channel, in the board's margins
(series 15 pF + shunt 47 nH toward RF, series 47 nH + shunt 15 pF toward IF, corner 200 MHz) in place of the
Passive, so the same tile up-converts a DAC tone (IF in, RF out) or down-converts an antenna's signal (RF in, IF out).

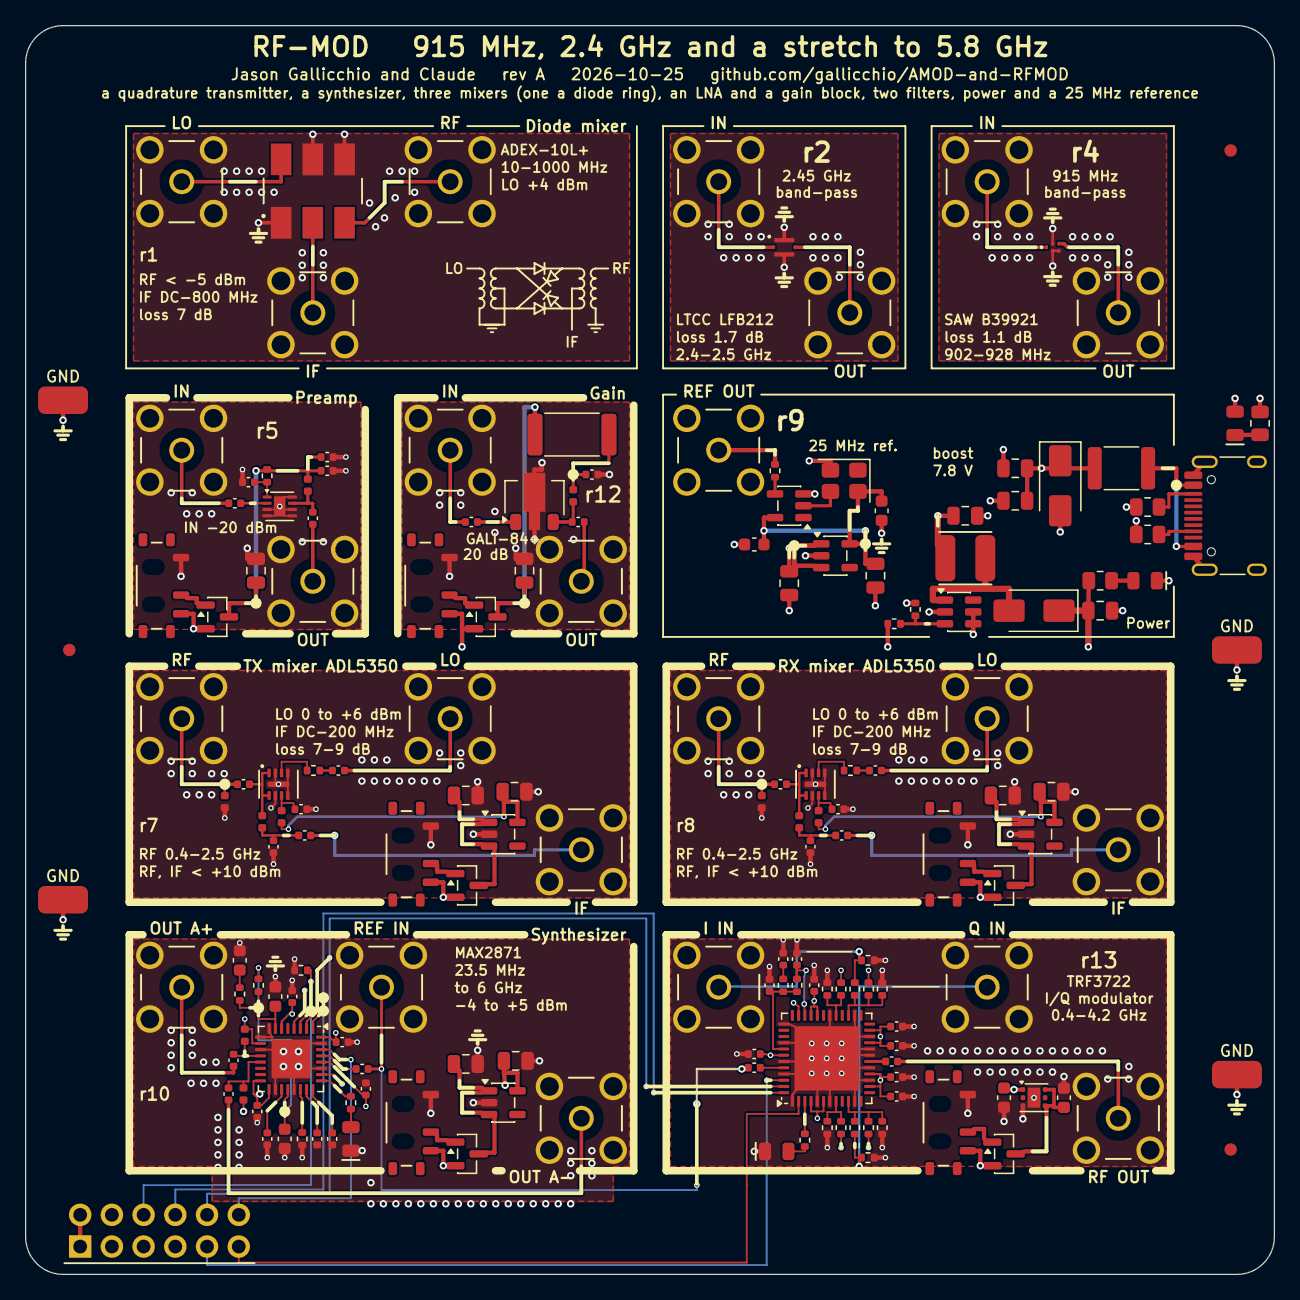
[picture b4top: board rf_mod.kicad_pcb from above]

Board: 4 copper layers, 100.0 x 100.0 mm, 168 parts (0 on the bottom side), 99 nets.
